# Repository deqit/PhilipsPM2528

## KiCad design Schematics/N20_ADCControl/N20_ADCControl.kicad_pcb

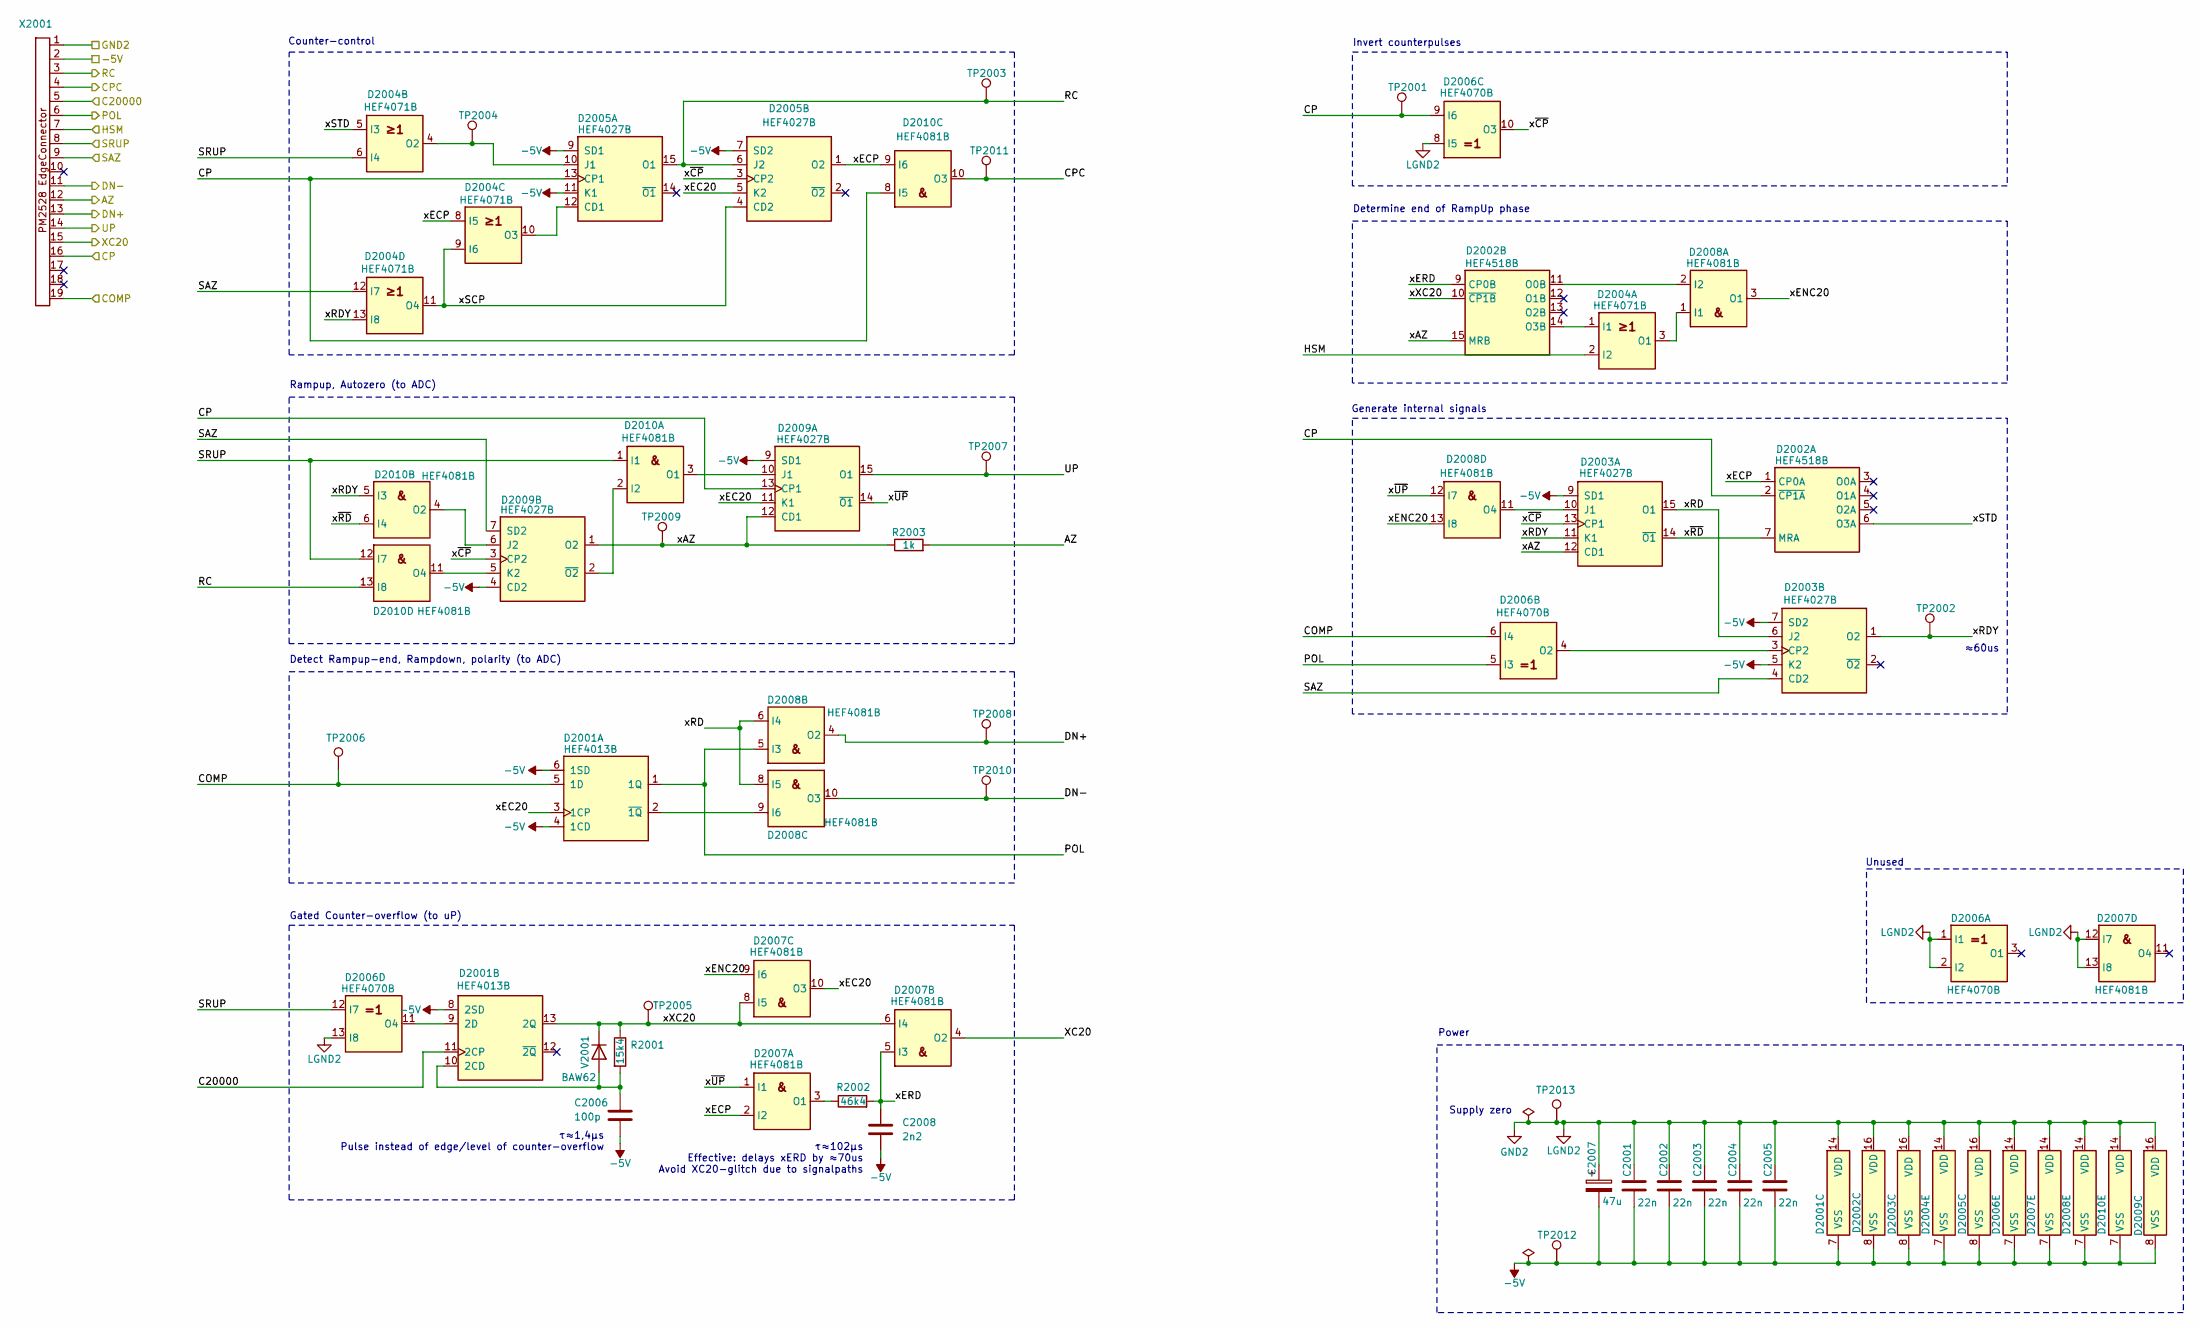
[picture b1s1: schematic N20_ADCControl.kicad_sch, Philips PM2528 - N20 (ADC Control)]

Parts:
C2001, C2002, C2003, C2004, C2005: 22n; C_Disc_D5.0mm_W2.5mm_P5.00mm
C2006: 100p; C_Disc_D5.0mm_W2.5mm_P5.00mm
C2007: 47u; CP_Axial_L10.0mm_D6.0mm_P15.00mm_Horizontal
C2008: 2n2; C_Disc_D5.0mm_W2.5mm_P5.00mm
D2001: HEF4013B; DIP-14_W7.62mm
D2002: HEF4518B; DIP-16_W7.62mm
D2003, D2005, D2009: HEF4027B; DIP-16_W7.62mm
D2004: HEF4071B; DIP-14_W7.62mm
D2006: HEF4070B; DIP-14_W7.62mm
D2007, D2008, D2010: HEF4081B; DIP-14_W7.62mm
R2001: 15k4; R_Axial_DIN0207_L6.3mm_D2.5mm_P10.16mm_Horizontal
R2002: 46k4; R_Axial_DIN0207_L6.3mm_D2.5mm_P10.16mm_Horizontal
R2003: 1k; R_Axial_DIN0207_L6.3mm_D2.5mm_P10.16mm_Horizontal
TP2001, TP2002, TP2003, TP2004, TP2005, TP2006, TP2007, TP2008, TP2010, TP2011, TP2012, TP2013: TestPoint; Pin_D0.9mm_L10.0mm_W2.4mm_FlatFork
TP2009: xAZ; Pin_D0.9mm_L10.0mm_W2.4mm_FlatFork
V2001: BAW62; D_DO-35_SOD27_P10.16mm_Horizontal
X2001: PM2528Edgeconnector

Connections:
-5V: C2001.2, C2002.2, C2003.2, C2004.2, C2005.2, C2006.2, C2007.2, C2008.2, D2001.4 (1CD), D2001.6 (1SD), D2001.7 (VSS), D2001.8 (2SD), D2002.8 (VSS), D2003.5 (K2), D2003.7 (SD2), D2003.8 (VSS), D2003.9 (SD1), D2004.7 (VSS), D2005.7 (SD2), D2005.8 (VSS), D2005.9 (SD1), D2005.11 (K1), D2006.7 (VSS), D2007.7 (VSS), D2008.7 (VSS), D2009.4 (CD2), D2009.8 (VSS), D2009.9 (SD1), D2010.7 (VSS), TP2012.1 (1_1), X2001.2
/AZ: R2003.2, X2001.12
/C20000: D2001.11 (2CP), X2001.5
/COMP: D2001.5 (1D), D2006.6 (I4), TP2006.1 (1_1), X2001.19
/CP: D2002.2 (~CP1A), D2005.13 (CP1), D2006.9 (I6), D2009.13 (CP1), D2010.8 (I5), TP2001.1 (1_1), X2001.16
/CPC: D2010.10 (O3), TP2011.1 (1_1), X2001.4
/DN+: D2008.4 (O2), TP2008.1 (1_1), X2001.13
/DN-: D2008.10 (O3), TP2010.1 (1_1), X2001.11
/HSM: D2004.2 (I2), X2001.7
/POL: D2001.1 (1Q), D2006.5 (I3), D2008.5 (I3), X2001.6
/RC: D2005.6 (J2), D2005.15 (O1), D2010.13 (I8), TP2003.1 (1_1), X2001.3
/SAZ: D2003.4 (CD2), D2004.12 (I7), D2009.7 (SD2), X2001.9
/SRUP: D2004.6 (I4), D2006.12 (I7), D2010.1 (I1), D2010.12 (I7), X2001.8
/UP: D2009.15 (O1), TP2007.1 (1_1), X2001.14
/XC20: D2007.4 (O2), X2001.15
/xAZ: D2002.15 (MRB), D2003.12 (CD1), D2009.1 (O2), D2009.12 (CD1), R2003.1, TP2009.1 (1_1)
/xEC20: D2001.3 (1CP), D2005.5 (K2), D2007.10 (O3), D2009.11 (K1)
/xECP: D2002.1 (CP0A), D2004.8 (I5), D2005.1 (O2), D2007.2 (I2), D2010.9 (I6)
/xENC20: D2007.9 (I6), D2008.3 (O1), D2008.13 (I8)
/xERD: C2008.1, D2002.9 (CP0B), D2007.5 (I3), R2002.2
/xRD: D2003.6 (J2), D2003.15 (O1), D2008.6 (I4), D2008.8 (I5)
/xRDY: D2003.1 (O2), D2003.11 (K1), D2004.13 (I8), D2010.5 (I3), TP2002.1 (1_1)
/xSCP: D2004.9 (I6), D2004.11 (O4), D2005.4 (CD2)
/xSTD: D2002.6 (O3A), D2004.5 (I3)
/xXC20: D2001.13 (2Q), D2002.10 (~CP1B), D2007.6 (I4), D2007.8 (I5), R2001.1, TP2005.1 (1_1), V2001.1 (K)
/x~CP: D2003.13 (CP1), D2005.3 (CP2), D2006.10 (O3), D2009.3 (CP2)
/x~RD: D2002.7 (MRA), D2003.14 (~O1), D2010.6 (I4)
/x~UP: D2007.1 (I1), D2008.12 (I7), D2009.14 (~O1)
GND2: C2001.1, C2002.1, C2003.1, C2004.1, C2005.1, C2007.1, D2001.14 (VDD), D2002.16 (VDD), D2003.16 (VDD), D2004.14 (VDD), D2005.16 (VDD), D2006.1 (I1), D2006.2 (I2), D2006.8 (I5), D2006.13 (I8), D2006.14 (VDD), D2007.12 (I7), D2007.13 (I8), D2007.14 (VDD), D2008.14 (VDD), D2009.16 (VDD), D2010.14 (VDD), TP2013.1 (1_1), X2001.1
unnamed: D2001.2 (~1Q), D2008.9 (I6)
unnamed: C2006.1, D2001.10 (2CD), R2001.2, V2001.2 (A)
unnamed: D2001.9 (2D), D2006.11 (O4)
unnamed: D2002.11 (O0B), D2008.2 (I2)
unnamed: D2002.14 (O3B), D2004.1 (I1)
unnamed: D2003.10 (J1), D2008.11 (O4)
unnamed: D2003.3 (CP2), D2006.4 (O2)
unnamed: D2004.3 (O1), D2008.1 (I1)
unnamed: D2004.4 (O2), D2005.10 (J1), TP2004.1 (1_1)
unnamed: D2004.10 (O3), D2005.12 (CD1)
unnamed: D2007.3 (O1), R2002.1
unnamed: D2009.10 (J1), D2010.3 (O1)
unnamed: D2009.6 (J2), D2010.4 (O2)
unnamed: D2009.5 (K2), D2010.11 (O4)
unnamed: D2009.2 (~O2), D2010.2 (I2)

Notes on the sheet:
τ≈102μs Effective: delays xERD by ≈70us Avoid XC20-glitch due to signalpaths
Rampup, Autozero (to ADC)
Determine end of RampUp phase
Detect Rampup-end, Rampdown, polarity (to ADC)
Power
Generate internal signals
Supply zero
Invert counterpulses
Counter-control
τ≈1,4μs Pulse instead of edge/level of counter-overflow
Gated Counter-overflow (to uP)
Unused
≈60us

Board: 2 copper layers, 36 parts (0 on the bottom side), 44 nets, no tracks yet.

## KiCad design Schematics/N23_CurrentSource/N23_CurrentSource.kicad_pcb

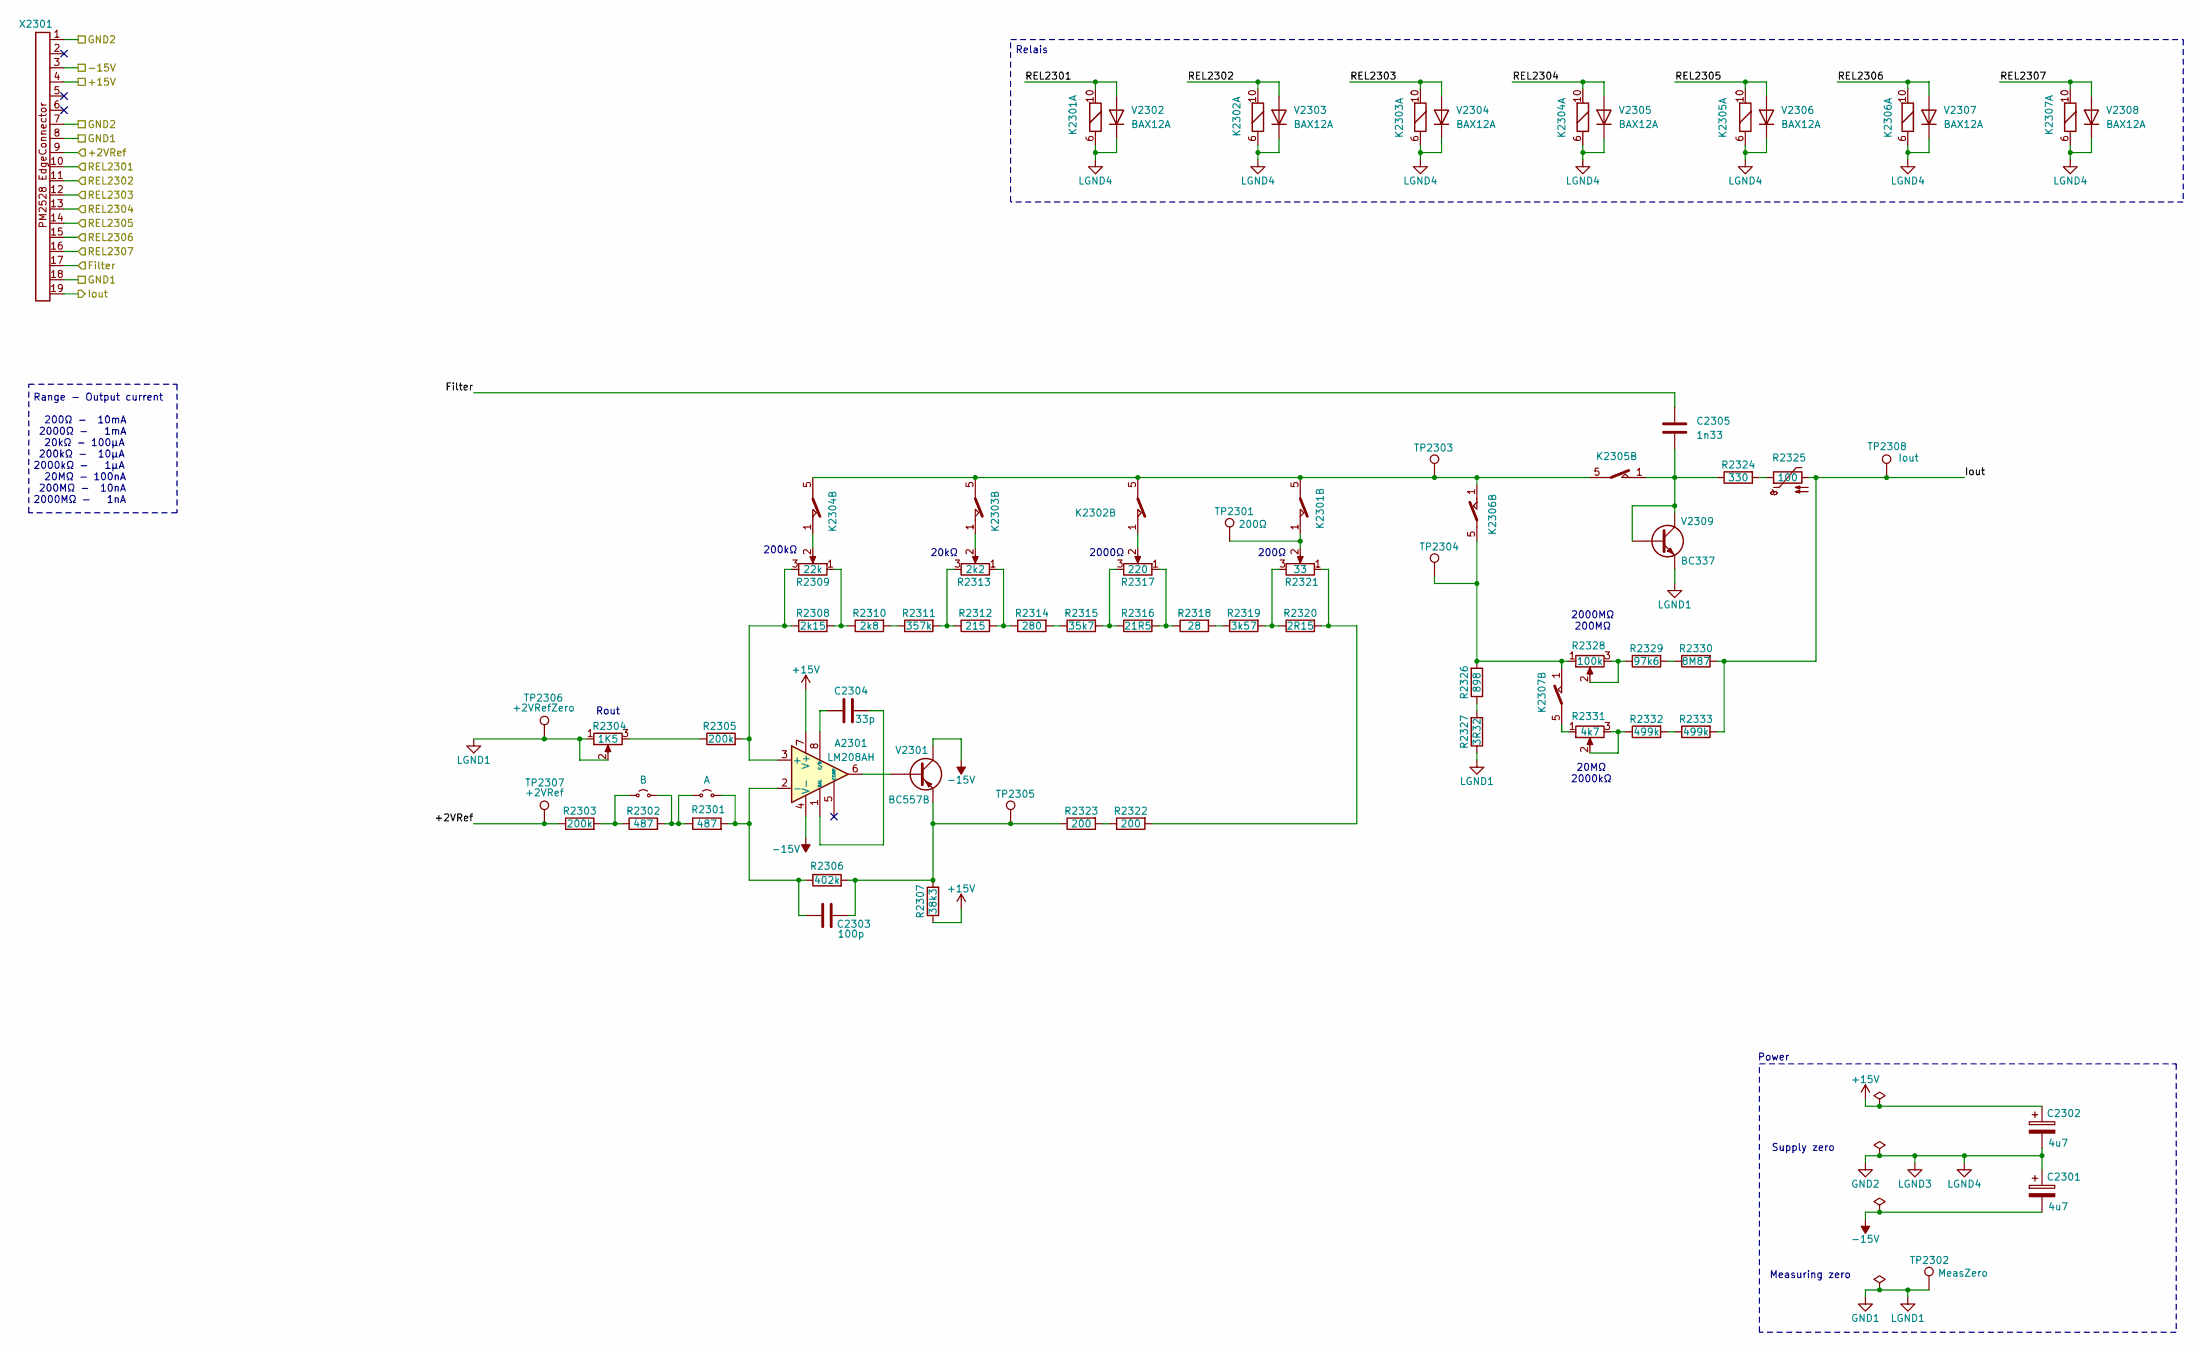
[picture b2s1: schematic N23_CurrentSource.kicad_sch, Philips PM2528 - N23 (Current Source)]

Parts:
A2301: LM208AH; TO-99-8
C2301, C2302: 4u7; CP_Radial_Tantal_D4.5mm_P5.00mm
C2303: 100p; C_Disc_D5.0mm_W2.5mm_P5.00mm
C2304: 33p; C_Disc_D4.3mm_W1.9mm_P5.00mm
C2305: 1n33; C_Axial_L5.1mm_D3.1mm_P15.00mm_Horizontal
JP2301: B; TestPoint_Bridge_Pitch5.08mm_Drill0.7mm
JP2302: A; TestPoint_Bridge_Pitch5.08mm_Drill0.7mm
K2301, K2302, K2303, K2304, K2305, K2306, K2307: Reed relay assy
R2301, R2302: 487; R_Axial_DIN0207_L6.3mm_D2.5mm_P10.16mm_Horizontal
R2303, R2305: 200k; R_Axial_DIN0309_L9.0mm_D3.2mm_P12.70mm_Horizontal
R2304: 1K5; Trimmer vertical
R2306: 402k; R_Axial_DIN0309_L9.0mm_D3.2mm_P12.70mm_Horizontal
R2307: 38k3; R_Axial_DIN0207_L6.3mm_D2.5mm_P10.16mm_Horizontal
R2308: 2k15; R_Axial_DIN0207_L6.3mm_D2.5mm_P10.16mm_Horizontal
R2309: 22k; Trimmer vertical
R2310: 2k8; R_Axial_DIN0207_L6.3mm_D2.5mm_P10.16mm_Horizontal
R2311: 357k; R_Axial_DIN0309_L9.0mm_D3.2mm_P12.70mm_Horizontal
R2312: 215; R_Axial_DIN0207_L6.3mm_D2.5mm_P10.16mm_Horizontal
R2313: 2k2; Trimmer vertical
R2314: 280; R_Axial_DIN0207_L6.3mm_D2.5mm_P10.16mm_Horizontal
R2315: 35k7; R_Axial_DIN0207_L6.3mm_D2.5mm_P10.16mm_Horizontal
R2316: 21R5; R_Axial_DIN0207_L6.3mm_D2.5mm_P10.16mm_Horizontal
R2317: 220; Trimmer vertical
R2318: 28; R_Axial_DIN0207_L6.3mm_D2.5mm_P10.16mm_Horizontal
R2319: 3k57; R_Axial_DIN0207_L6.3mm_D2.5mm_P10.16mm_Horizontal
R2320: 2R15; R_Axial_DIN0207_L6.3mm_D2.5mm_P10.16mm_Horizontal
R2321: 33; Trimmer vertical
R2322, R2323: 200; R_Axial_DIN0309_L9.0mm_D3.2mm_P12.70mm_Horizontal
R2324: 330; R_Axial_DIN0614_L14.3mm_D5.7mm_P25.40mm_Horizontal
R2325: 100; RV_Disc_D7mm_W3.9mm_P5mm
R2326: 898; R_Axial_DIN0207_L6.3mm_D2.5mm_P10.16mm_Horizontal
R2327: 3R32; R_Axial_DIN0207_L6.3mm_D2.5mm_P10.16mm_Horizontal
R2328: 100k; Trimmer vertical
R2329: 97k6; R_Axial_DIN0207_L6.3mm_D2.5mm_P10.16mm_Horizontal
R2330: 8M87; R_Axial_DIN0411_L9.9mm_D3.6mm_P15.24mm_Horizontal
R2331: 4k7; Trimmer vertical
R2332, R2333: 499k; R_Axial_DIN0309_L9.0mm_D3.2mm_P12.70mm_Horizontal
TP2301: 200Ω; Pin_D0.9mm_L10.0mm_W2.4mm_FlatFork
TP2302: MeasZero; Pin_D0.9mm_L10.0mm_W2.4mm_FlatFork
TP2303, TP2304, TP2305: Pin_D0.9mm_L10.0mm_W2.4mm_FlatFork
TP2306: +2VRefZero; Pin_D0.9mm_L10.0mm_W2.4mm_FlatFork
TP2307: +2VRef; Pin_D0.9mm_L10.0mm_W2.4mm_FlatFork
TP2308: Iout; Pin_D0.9mm_L10.0mm_W2.4mm_FlatFork
V2301: BC557B; TO-92_Inline
V2302: BAX12A; D_DO-41_SOD81_P10.16mm_Horizontal
V2303, V2304, V2305, V2306, V2307, V2308: BAX12A; D_DO-34_SOD68_P10.16mm_Horizontal
V2309: BC337; TO-92_Inline
X2301: PM2528Edgeconnector

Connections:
+15V: A2301.7 (V+), C2302.1, R2307.1, X2301.4
-15V: A2301.4 (V-), C2301.2, V2301.1 (C), X2301.3
/+2VRef: R2303.1, TP2307.1 (1_1), X2301.9
/Filter: C2305.2, X2301.17
/Iout: R2325.2, R2330.2, R2333.2, TP2308.1 (1_1), X2301.19
/REL2301: K2301.10, V2302.2 (A), X2301.10
/REL2302: K2302.10, V2303.2 (A), X2301.11
/REL2303: K2303.10, V2304.2 (A), X2301.12
/REL2304: K2304.10, V2305.2 (A), X2301.13
/REL2305: K2305.10, V2306.2 (A), X2301.14
/REL2306: K2306.10, V2307.2 (A), X2301.15
/REL2307: K2307.10, V2308.2 (A), X2301.16
GND1: R2304.1, R2304.2, R2327.1, TP2302.1 (1_1), TP2306.1 (1_1), V2309.3 (E), X2301.8, X2301.18
GND2: C2301.1, C2302.2, K2301.6, K2302.6, K2303.6, K2304.6, K2305.6, K2306.6, K2307.6, V2302.1 (K), V2303.1 (K), V2304.1 (K), V2305.1 (K), V2306.1 (K), V2307.1 (K), V2308.1 (K), X2301.1, X2301.7
unnamed: A2301.3 (+), R2305.2, R2308.1, R2309.3
unnamed: A2301.2 (-), C2303.2, JP2302.2 (B), R2301.2, R2306.1
unnamed: A2301.1 (BAL), C2304.2
unnamed: A2301.8 (C/B), C2304.1
unnamed: JP2301.1 (A_1), R2302.1, R2303.2
unnamed: JP2301.2 (B), JP2302.1 (A_1), R2301.1, R2302.2
unnamed: K2301.1, R2321.2, TP2301.1 (1_1)
unnamed: K2301.5, K2302.5, K2303.5, K2304.5, K2305.5, K2306.1, TP2303.1 (1_1)
unnamed: K2302.1, R2317.2
unnamed: K2303.1, R2313.2
unnamed: K2304.1, R2309.2
unnamed: K2306.5, K2307.1, R2326.2, R2328.1, TP2304.1 (1_1)
unnamed: K2307.5, R2331.1
unnamed: R2304.3, R2305.1
unnamed: R2308.2, R2309.1, R2310.1
unnamed: R2310.2, R2311.1
unnamed: R2311.2, R2312.1, R2313.3
unnamed: R2312.2, R2313.1, R2314.1
unnamed: R2314.2, R2315.1
unnamed: R2315.2, R2316.1, R2317.3
unnamed: R2316.2, R2317.1, R2318.1
unnamed: R2318.2, R2319.1
unnamed: R2319.2, R2320.1, R2321.3
unnamed: R2320.2, R2321.1, R2322.2
unnamed: R2322.1, R2323.2
unnamed: R2324.2, R2325.1
unnamed: R2326.1, R2327.2
unnamed: R2328.2, R2328.3, R2329.1
unnamed: R2329.2, R2330.1
unnamed: R2331.2, R2331.3, R2332.1
unnamed: R2332.2, R2333.1
unnamed: A2301.6, V2301.2 (B)
unnamed: C2303.1, R2306.2, R2307.2, R2323.1, TP2305.1 (1_1), V2301.3 (E)
unnamed: C2305.1, K2305.1, R2324.1, V2309.1 (C), V2309.2 (B)

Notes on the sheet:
200Ω
Power
Measuring zero
20kΩ
2000MΩ 200MΩ
200kΩ
20MΩ 2000kΩ
Relais
2000Ω
Rout
Range - Output current 200Ω - 10mA 2000Ω - 1mA 20kΩ - 100µA 200kΩ - 10µA 2000kΩ - 1µA 20MΩ - 100nA 200MΩ - 10nA 2000MΩ - 1nA
Supply zero

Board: 2 copper layers, 66 parts (0 on the bottom side), 48 nets, no tracks yet.

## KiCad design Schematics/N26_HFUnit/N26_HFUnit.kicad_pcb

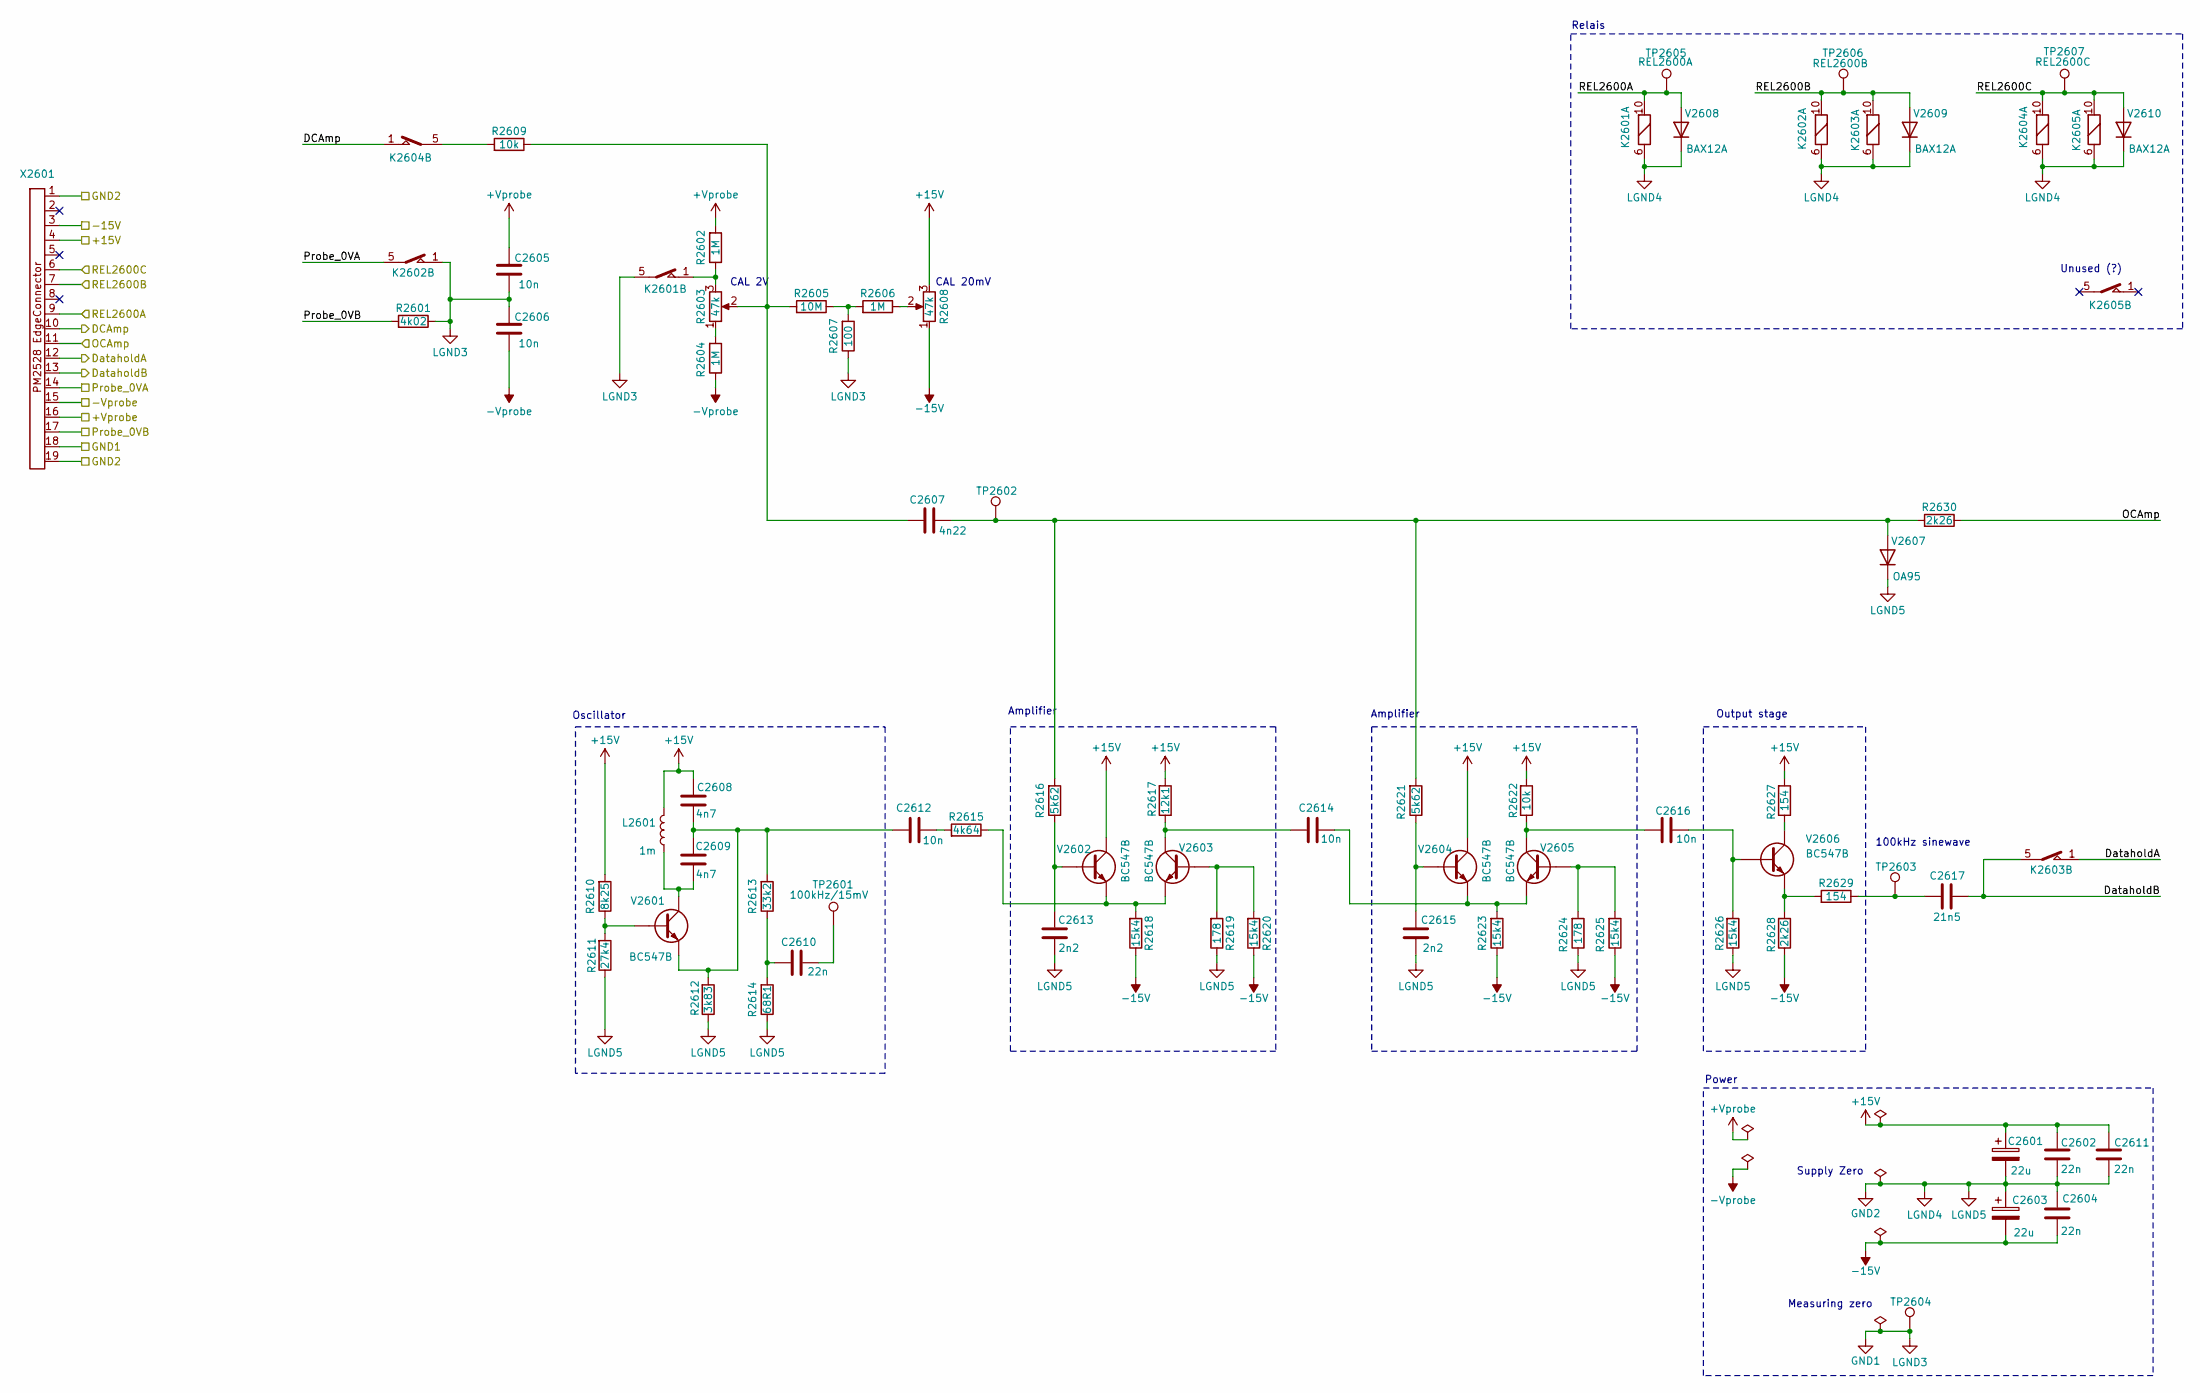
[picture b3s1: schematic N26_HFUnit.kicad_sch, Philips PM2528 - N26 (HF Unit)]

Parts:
C2601, C2603: 22u; CP_Axial_L10.0mm_D4.5mm_P15.00mm_Horizontal
C2602, C2604, C2610, C2611: 22n; C_Disc_D5.0mm_W2.5mm_P5.00mm
C2605, C2606, C2612, C2614, C2616: 10n; C_Disc_D5.0mm_W2.5mm_P5.00mm
C2607: 4n22; C_Axial_L5.1mm_D3.1mm_P15.00mm_Horizontal
C2608, C2609: 4n7; C_Disc_D5.0mm_W2.5mm_P5.00mm
C2613, C2615: 2n2; C_Disc_D5.0mm_W2.5mm_P5.00mm
C2617: 21n5; C_Axial_L12.0mm_D7.5mm_P20.00mm_Horizontal
K2601, K2602, K2603, K2604, K2605: Reed relay assy
L2601: 1m; L_Axial_L9.5mm_D4.0mm_P15.24mm_Horizontal_Fastron_SMCC
R2601: 4k02; R_Axial_DIN0207_L6.3mm_D2.5mm_P10.16mm_Horizontal
R2602, R2604, R2606: 1M; R_Axial_DIN0309_L9.0mm_D3.2mm_P15.24mm_Horizontal
R2603, R2608: 47k; Trimmer vertical
R2605: 10M; R_Axial_DIN0207_L6.3mm_D2.5mm_P10.16mm_Horizontal
R2607: 100; R_Axial_DIN0207_L6.3mm_D2.5mm_P10.16mm_Horizontal
R2609, R2622: 10k; R_Axial_DIN0207_L6.3mm_D2.5mm_P10.16mm_Horizontal
R2610: 8k25; R_Axial_DIN0207_L6.3mm_D2.5mm_P10.16mm_Horizontal
R2611: 27k4; R_Axial_DIN0207_L6.3mm_D2.5mm_P10.16mm_Horizontal
R2612: 3k83; R_Axial_DIN0207_L6.3mm_D2.5mm_P10.16mm_Horizontal
R2613: 33k2; R_Axial_DIN0207_L6.3mm_D2.5mm_P10.16mm_Horizontal
R2614: 68R1; R_Axial_DIN0207_L6.3mm_D2.5mm_P10.16mm_Horizontal
R2615: 4k64; R_Axial_DIN0207_L6.3mm_D2.5mm_P10.16mm_Horizontal
R2616, R2621: 5k62; R_Axial_DIN0207_L6.3mm_D2.5mm_P10.16mm_Horizontal
R2617: 12k1; R_Axial_DIN0207_L6.3mm_D2.5mm_P10.16mm_Horizontal
R2618, R2620, R2623, R2625, R2626: 15k4; R_Axial_DIN0207_L6.3mm_D2.5mm_P10.16mm_Horizontal
R2619, R2624: 178; R_Axial_DIN0207_L6.3mm_D2.5mm_P10.16mm_Horizontal
R2627, R2629: 154; R_Axial_DIN0207_L6.3mm_D2.5mm_P10.16mm_Horizontal
R2628, R2630: 2k26; R_Axial_DIN0207_L6.3mm_D2.5mm_P10.16mm_Horizontal
TP2601: 100kHz/15mV; Pin_D0.9mm_L10.0mm_W2.4mm_FlatFork
TP2602, TP2603, TP2604: TestPoint; Pin_D0.9mm_L10.0mm_W2.4mm_FlatFork
TP2605: REL2600A; Pin_D0.9mm_L10.0mm_W2.4mm_FlatFork
TP2606: REL2600B; Pin_D0.9mm_L10.0mm_W2.4mm_FlatFork
TP2607: REL2600C; Pin_D0.9mm_L10.0mm_W2.4mm_FlatFork
V2601, V2602, V2603, V2604, V2605, V2606: BC547B; TO-92_Inline
V2607: OA95; D_DO-41_SOD81_P10.16mm_Horizontal
V2608, V2609, V2610: BAX12A; D_DO-34_SOD68_P10.16mm_Horizontal
X2601: PM2528Edgeconnector

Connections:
+15V: C2601.1, C2602.1, C2608.1, C2611.1, L2601.1, R2608.3, R2610.2, R2617.2, R2622.2, R2627.2, V2602.1 (C), V2604.1 (C), X2601.4
+Vprobe: C2605.1, R2602.2, X2601.16
-15V: C2603.2, C2604.2, R2608.1, R2618.1, R2620.1, R2623.1, R2625.1, R2628.1, X2601.3
-Vprobe: C2606.2, R2604.1, X2601.15
/DCAmp: K2604.1, X2601.10
/DataholdA: K2603.1, X2601.12
/DataholdB: C2617.1, K2603.5, X2601.13
/OCAmp: R2630.1, X2601.11
/Probe_0VA: K2602.5, X2601.14
/Probe_0VB: R2601.2, X2601.17
/REL2600A: K2601.10, TP2605.1 (1_1), V2608.2 (A), X2601.9
/REL2600B: K2602.10, K2603.10, TP2606.1 (1_1), V2609.2 (A), X2601.7
/REL2600C: K2604.10, K2605.10, TP2607.1 (1_1), V2610.2 (A), X2601.6
GND1: C2605.2, C2606.1, K2601.5, K2602.1, R2601.1, R2607.1, TP2604.1 (1_1), X2601.18
GND2: C2601.2, C2602.2, C2603.1, C2604.1, C2611.2, C2613.1, C2615.1, K2601.6, K2602.6, K2603.6, K2604.6, K2605.6, R2611.1, R2612.1, R2614.1, R2619.1, R2624.1, R2626.1, V2607.1 (K), V2608.1 (K), V2609.1 (K), V2610.1 (K), X2601.1, X2601.19
unnamed: C2607.1, R2603.2, R2605.2, R2609.1
unnamed: C2610.1, R2613.1, R2614.2
unnamed: C2610.2, TP2601.1 (1_1)
unnamed: C2612.1, R2615.2
unnamed: C2617.2, R2629.1, TP2603.1 (1_1)
unnamed: K2601.1, R2602.1, R2603.3
unnamed: K2604.5, R2609.2
unnamed: R2603.1, R2604.2
unnamed: R2605.1, R2606.2, R2607.2
unnamed: R2606.1, R2608.2
unnamed: R2610.1, R2611.2, V2601.2 (B)
unnamed: C2609.2, L2601.2, V2601.1 (C)
unnamed: C2608.2, C2609.1, C2612.2, R2612.2, R2613.2, V2601.3 (E)
unnamed: C2613.2, R2616.1, V2602.2 (B)
unnamed: R2615.1, R2618.2, V2602.3 (E), V2603.3 (E)
unnamed: R2619.2, R2620.2, V2603.2 (B)
unnamed: C2614.2, R2617.1, V2603.1 (C)
unnamed: C2615.2, R2621.1, V2604.2 (B)
unnamed: C2614.1, R2623.2, V2604.3 (E), V2605.3 (E)
unnamed: R2624.2, R2625.2, V2605.2 (B)
unnamed: C2616.2, R2622.1, V2605.1 (C)
unnamed: C2616.1, R2626.2, V2606.2 (B)
unnamed: R2627.1, V2606.1 (C)
unnamed: R2628.2, R2629.2, V2606.3 (E)
unnamed: C2607.2, R2616.2, R2621.2, R2630.2, TP2602.1 (1_1), V2607.2 (A)

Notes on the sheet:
Relais
Amplifier
Measuring zero
CAL 20mV
Oscillator
100kHz sinewave
CAL 2V
Output stage
Power
Supply Zero
Unused (?)

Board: 2 copper layers, 71 parts (0 on the bottom side), 40 nets, no tracks yet.
